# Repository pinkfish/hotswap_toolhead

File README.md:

# hotswap_toolhead (CAN stack, branch `can-stack`)

A CAN toolhead for 3D printers on two stacked boards. It drives a heater (up to 100 W) and a 24 V fan, and reads a thermistor (100k NTC or PT1000) and a switch. 24 V and the CAN bus come in on one small JST-XH plug. It runs Klipper over CAN on an STM32G0B1.

- **Boards:** two 25 × 26 mm, 4-layer boards, stacked 11 mm apart on a 2 × 4 board-to-board link: the logic board (MCU, CAN, USB, fan, sensors, 24 V input) on top and the power board (heater driver, 3.3 V buck) under it. Both have two M2 half-hole notches on their side edges for standoffs.
- **Plugs, all JST:**
  - Logic board, 6-pin XH on the top edge: 24 V and GND on two contacts each, CAN-H, CAN-L.
  - Logic board, 6-pin SH (1 mm) on the bottom edge: fan, thermistor, switch.
  - Logic board, 4-pin SH on the left edge: USB (VBUS, D−, D+, GND), wired to a USB socket for the first flash.
  - Power board, 4-pin XH on the bottom edge: the heater, two contacts per side.
- **Power:** an 8 A fuse and a TVS on the 24 V input, with no reverse-polarity FET (the plug is keyed). A 3.3 V buck runs the logic from 24 V or from USB alone.
- **Other branches:**
  - `can-sh` is the same circuit on one 27 × 34 mm board.
  - `usb-sh` is the USB-only board that one is built on: 19.5 × 23.5 mm, no heater.
  - `usb-only` is that board's first version.
  - `stack` is the 24 V CAN version as two stacked 27 × 27 mm boards, with XT30 and Nano-Fit plugs.
  - `narrow-27` and `centre-j2` are the earlier single-board 24 V versions.

## Repository layout

| Folder | Contents |
| --- | --- |
| `docs/` | Design spec (`design_spec.md`), with the Klipper config |
| `hardware/` | KiCad projects `toolhead_logic` and `toolhead_power`: schematics, routed PCBs, design rules, JLCPCB BOMs. `panel/`, `panel6/` and `panel4/` are the panels to order, each holding both boards |
| `gerber/` | Fab outputs. `logic/` and `power/` are the single boards, for checking. `panel/` (9 pairs), `panel6/` (6) and `panel4/` (4) are what you order: see `gerber/README.md` |
| `tools/` | See below |

What's in `tools/`:

- `design.py`: the netlist.
- `gen_kicad.py`: builds the schematic, BOM and rules from it.
- `verify.py`: checks every pin's net, and that the link's two halves match.
- `check_stack.py`: checks that the routed boards stack (outline, notches, link pins).
- `fab.sh`: regenerates `gerber/logic/` and `gerber/power/`.
- `make_panel.sh`: builds the panels.
- `layout/`: the placement and routing scripts (see `tools/layout/README.md`).

## Status

The schematic is complete and the PCB is routed:

- DRC: 0 errors, 0 unconnected, schematic parity clean, on both boards.
- `check_stack.py`: the boards stack.
- All three panels build with 0 DRC errors.

Nothing has been built or tested yet. See the prototype checks at the end of `docs/design_spec.md`, and note that the board has no reverse-polarity protection.

## Regenerating the KiCad files

```
python3 tools/gen_kicad.py   # rebuilds both schematics, BOMs and rules from tools/design.py
python3 tools/verify.py      # re-parses the schematic and checks every pin's net
```

The generator never touches the routed board. After a netlist change, choose one:

- Run **Update PCB from Schematic** in KiCad and fix up the routing.
- Re-run the layout (`tools/layout/run_stack.sh logic|power`).

Then run `tools/check_stack.py`, `tools/fab.sh` and `tools/make_panel.sh` (9, 6 and 4).

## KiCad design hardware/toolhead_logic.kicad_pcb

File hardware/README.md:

# CAN toolhead stack – KiCad projects

`tools/gen_kicad.py` generates both schematics from `tools/design.py`, the netlist. The PCBs are routed. The projects open in KiCad 8 or newer; they were routed and checked in KiCad 10.

## What's here

| File | Contents |
| --- | --- |
| `toolhead_logic.kicad_pro`, `.kicad_sch`, `.kicad_pcb`, `.kicad_dru` | The logic board (upper): 46 parts. Power input, MCU, CAN, USB, the plug J2, fan, thermistor, switch, the link socket J6. 25 × 26 mm, 4 layers, two M2 edge notches |
| `toolhead_power.kicad_pro`, `.kicad_sch`, `.kicad_pcb`, `.kicad_dru` | The power board (lower): 19 parts. The heater plug J3, heater FET and gate driver, 3.3 V buck, the link header J7. Same outline and notches |
| `toolhead_logic-bom-jlcpcb.csv`, `toolhead_power-bom-jlcpcb.csv`, `bom_jlcpcb.csv` | BOMs in JLCPCB's upload format, per board and for both together. The solder-jumper pads (JP1–JP3) are left out; every other part is placed |
| `panel/`, `panel6/`, `panel4/` | The panels to order: 9, 6 or 4 logic/power pairs, built by `../tools/make_panel.sh` |
| `fp-lib-table`, `footprints/` | Project footprint library: Q2's AOS DFN 3 × 3 footprint |

Netclasses (both boards): Power 0.8 / 0.3 mm, Fan 0.4 / 0.3 mm, Supply and USB 0.3 / 0.2 mm. The design rules add 0.8 mm minimum on the high-current nets, 0.3 mm clearance on the 24 V nets, the USB pair and the fan current.

`tools/verify.py` re-parses both schematics and rebuilds the netlists from pin and label positions: every pin matches `tools/design.py`, no pin is left dangling, and J6 and J7 carry the same net on every pin. `tools/check_stack.py` checks the routed boards: same outline and notches, and every J7 pin under its J6 contact.

## Layout

| Board | Layer | What's on it |
| --- | --- | --- |
| Logic | F.Cu | J1, J2, J5; F1, D1, F2; Q3, D5, R15, R16; LED1/LED2 with R5/R6. VIN_RAW and +24V pours. GND fill |
| Logic | B.Cu | U6 with Y1, FB1 and C9, C11–C15; CAN (U3, D4, R11, JP1, C16); J6; U5, C17, D3; C1; JP3 with R4, C10; the thermistor network and switch filter; SW1. +24V and GND pours on J6. GND fill |
| Power | F.Cu | J7, J3, Q2, U7 with R13, D10, C21, R14; C2; the buck (U1, L1, D9, D7, C4–C6, C8, R2, R3). +24V, HEAT_N and GND pours. GND fill |
| Power | B.Cu | GND fill; J7's pin ends |
| Both | In1 / In2 | Solid GND / signals |

- **Reference designators:** most bottom-side ones are on B.Fab rather than the silkscreen, because there is no room for them. They still appear on assembly drawings.

## Check against datasheets

- **J1 (JST S6B-XH-SM4-TB):** seen from the top with the plug opening at the top edge, pin 1 is on the right. 1–2 +24V, 3–4 GND, 5 CAN-H, 6 CAN-L.
- **J2 (JST SM06B-SRSS-TB):** plug opening at the bottom edge, pin 1 on the left. 1 FAN+, 2 FAN−, 3 TH_SIG, 4 thermistor GND, 5 SENS, 6 GND.
- **J5 (JST SM04B-SRSS-TB):** plug opening at the left edge, pin 1 at the top. 1 VBUS, 2 D−, 3 D+, 4 GND.
- **J3 (JST S4B-XH-SM4-TB, power board):** plug opening at the bottom edge, pin 1 on the left. 1–2 HEAT− (Q2's drain), 3–4 +24V.
- **J6/J7 (the link):** 1–2 +24V, 3, 4 and 6 GND, 5 VIN_LOGIC, 7 HEAT_PWM, 8 +3V3.
- **U1 (LMR16006XDDC):** 1 CB, 2 GND, 3 FB, 4 SHDN, 5 VIN, 6 SW.
- **U3 (TCAN3414DRBR):** 1 TXD, 2 GND, 3 VDD, 4 RXD, 5 SHDN (open), 6 CANL, 7 CANH, 8 STB (GND).
- **U7 (UCC27517DBVR):** 1 VDD, 2 GND, 3 IN+, 4 IN−, 5 OUT.
- **U6 STM32G0B1 pinout:** VREF+ 5, VDD/VDDA 6, VSS/VSSA 7, PB0/PB1 19/20, PB12/PB13 24/25, PA11/12 33/34, PA14/PA15 36/37, PD0 38, PB3 42. Confirm against ST DS13560.
- **Crystal Y1:** 20 pF load with 33 pF caps. Check the oscillator's gain margin (ST AN2867) on the first board.

## Net names

| Net | What it is |
| --- | --- |
| `VIN_RAW` | 24 V from J1, before F1 |
| `+24V` | After F1: the fan, the link to the heater and D7 |
| `HEAT_N` | Q2's drain, the heater's low side |
| `VIN_LOGIC` | The buck's input: +24V through D7 or VBUS through D3 |
| `GATE_12V` | U7's zener-clamped supply |
| `HEAT_PWM` | PD0 to U7, across the link |
| `VBUS` | USB 5 V from J5 |
| `+3V3` | The buck's output, across the link |
| `VREFP` | The ferrite-filtered ADC reference and thermistor pull-up |
| `CAN_H` / `CAN_L` | The bus |
| `FAN_P` / `FAN_N` | The fan + after F2, and Q3's drain |
| `TH_SIG` / `TH_ADC` | The thermistor, before and after its filter |
| `SENS` / `SENS_IN` | The switch, before and after its filter |

## Fab outputs

`../tools/fab.sh` exports `../gerber/logic/` and `../gerber/power/` with `kicad-cli`: 4-layer gerbers, drill files, the BOM and the CPL. `tools/jlc_cpl.py` writes each CPL by fitting each part's own JLCPCB footprint onto its pads. The panels are in `../gerber/panel*/`. `../gerber/README.md` says which files to upload.

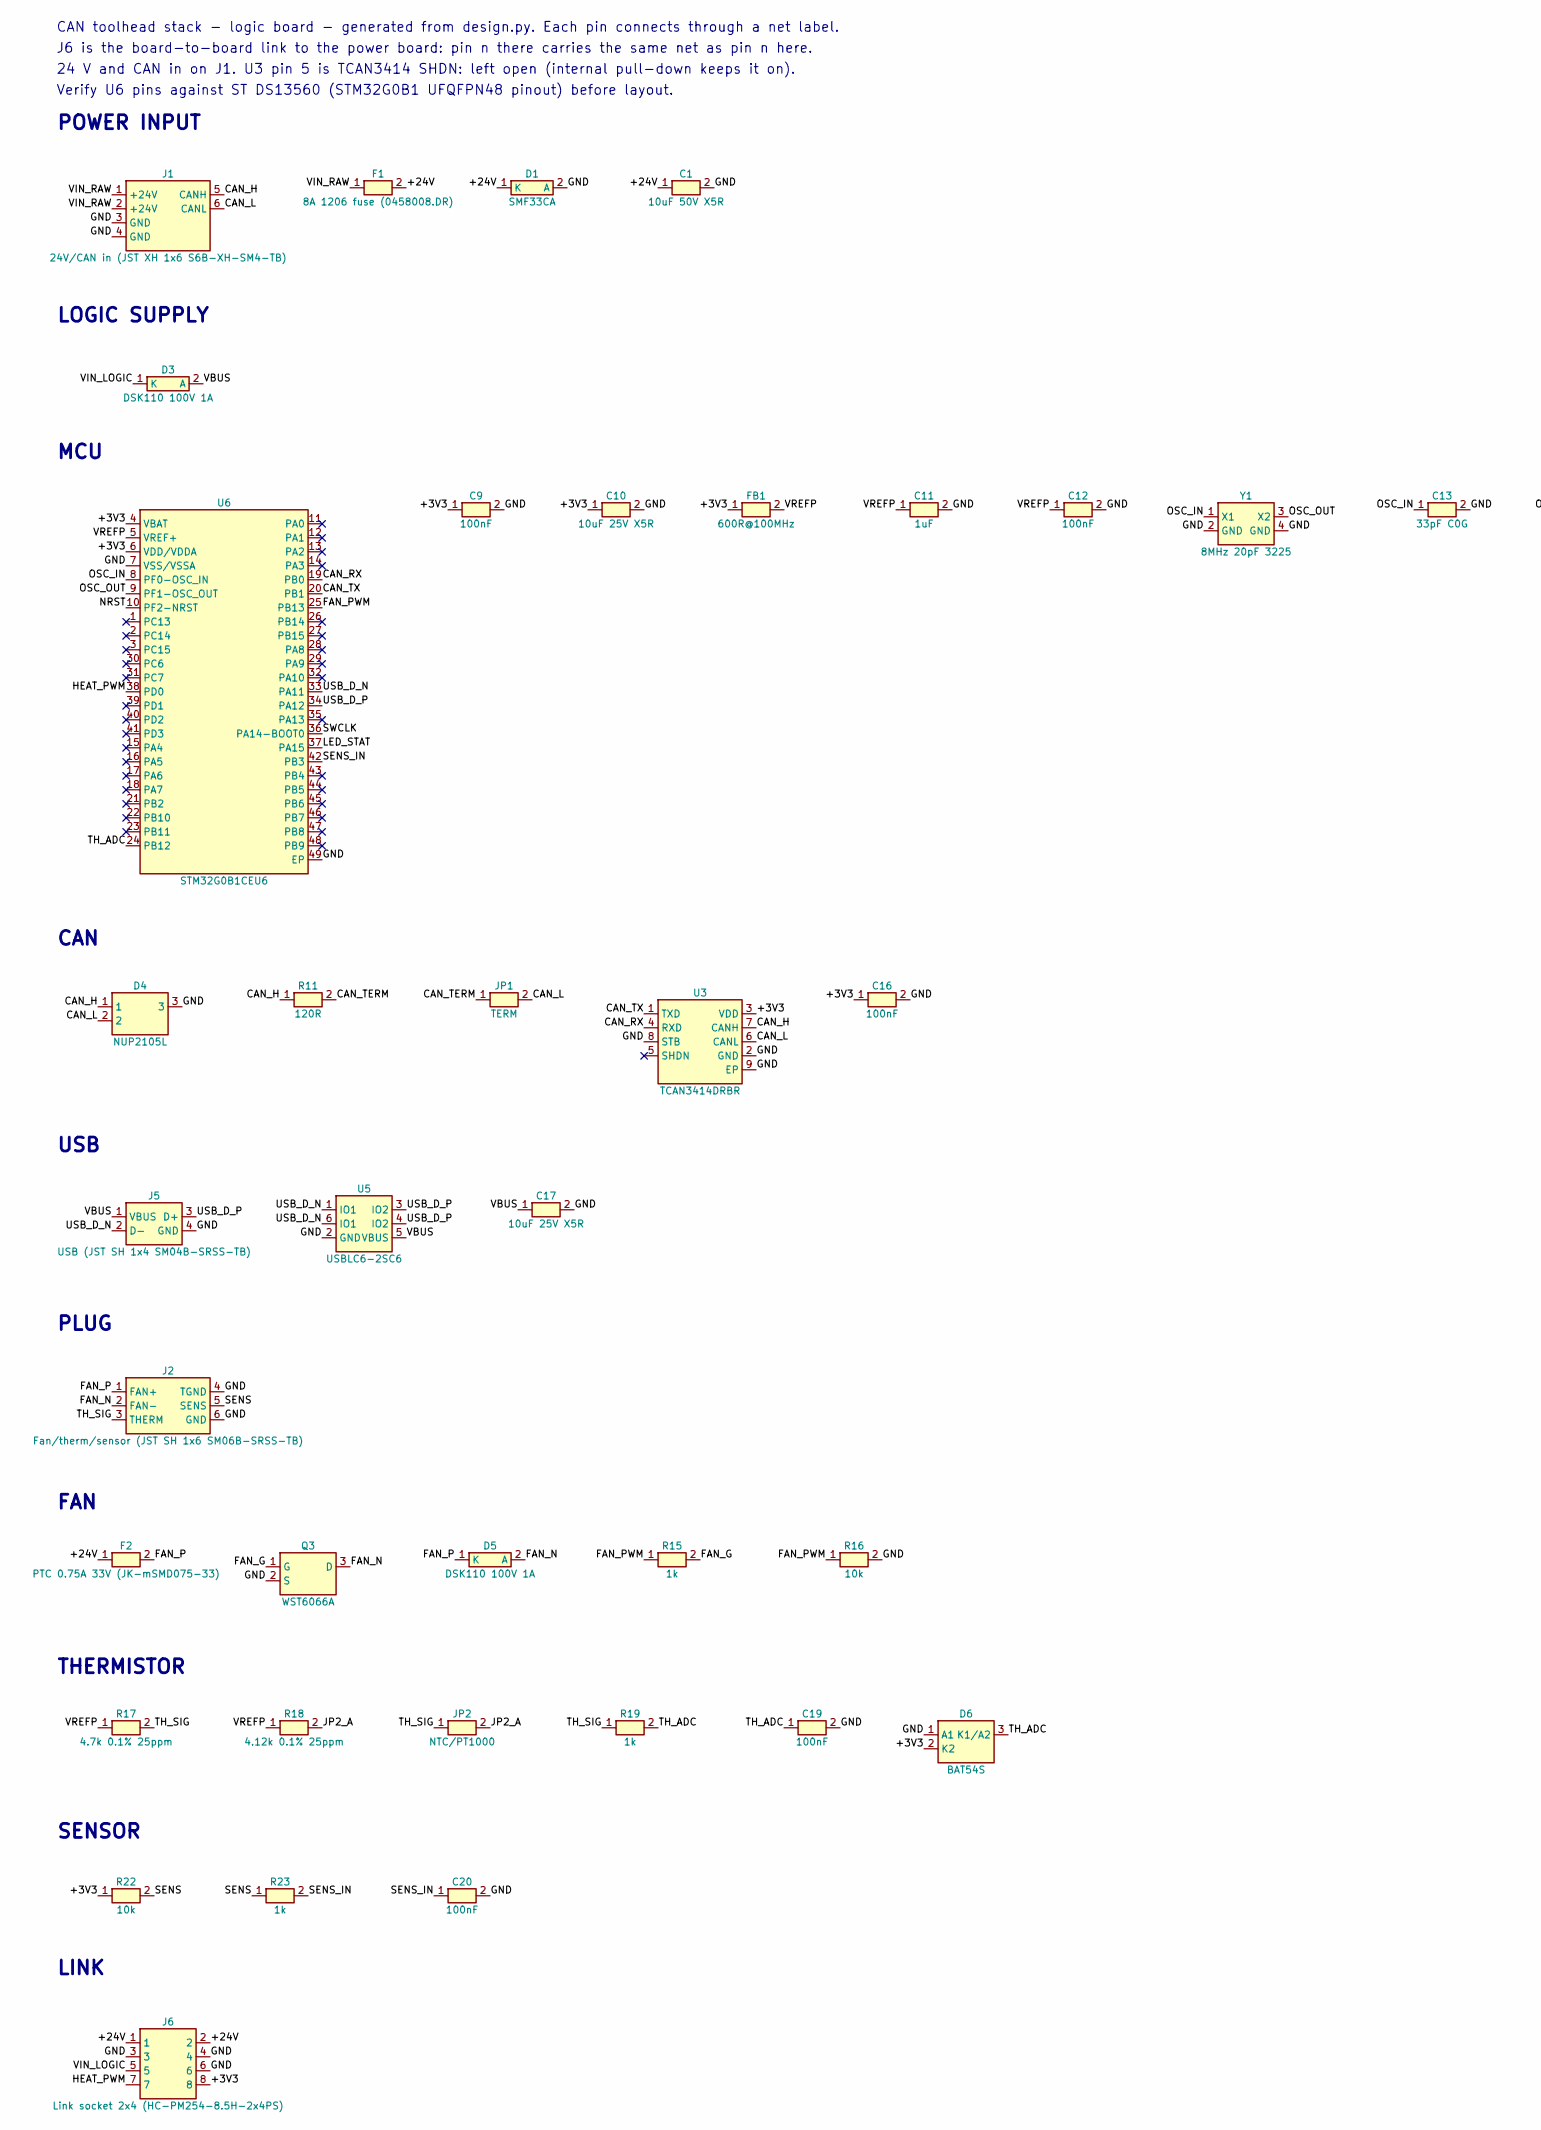
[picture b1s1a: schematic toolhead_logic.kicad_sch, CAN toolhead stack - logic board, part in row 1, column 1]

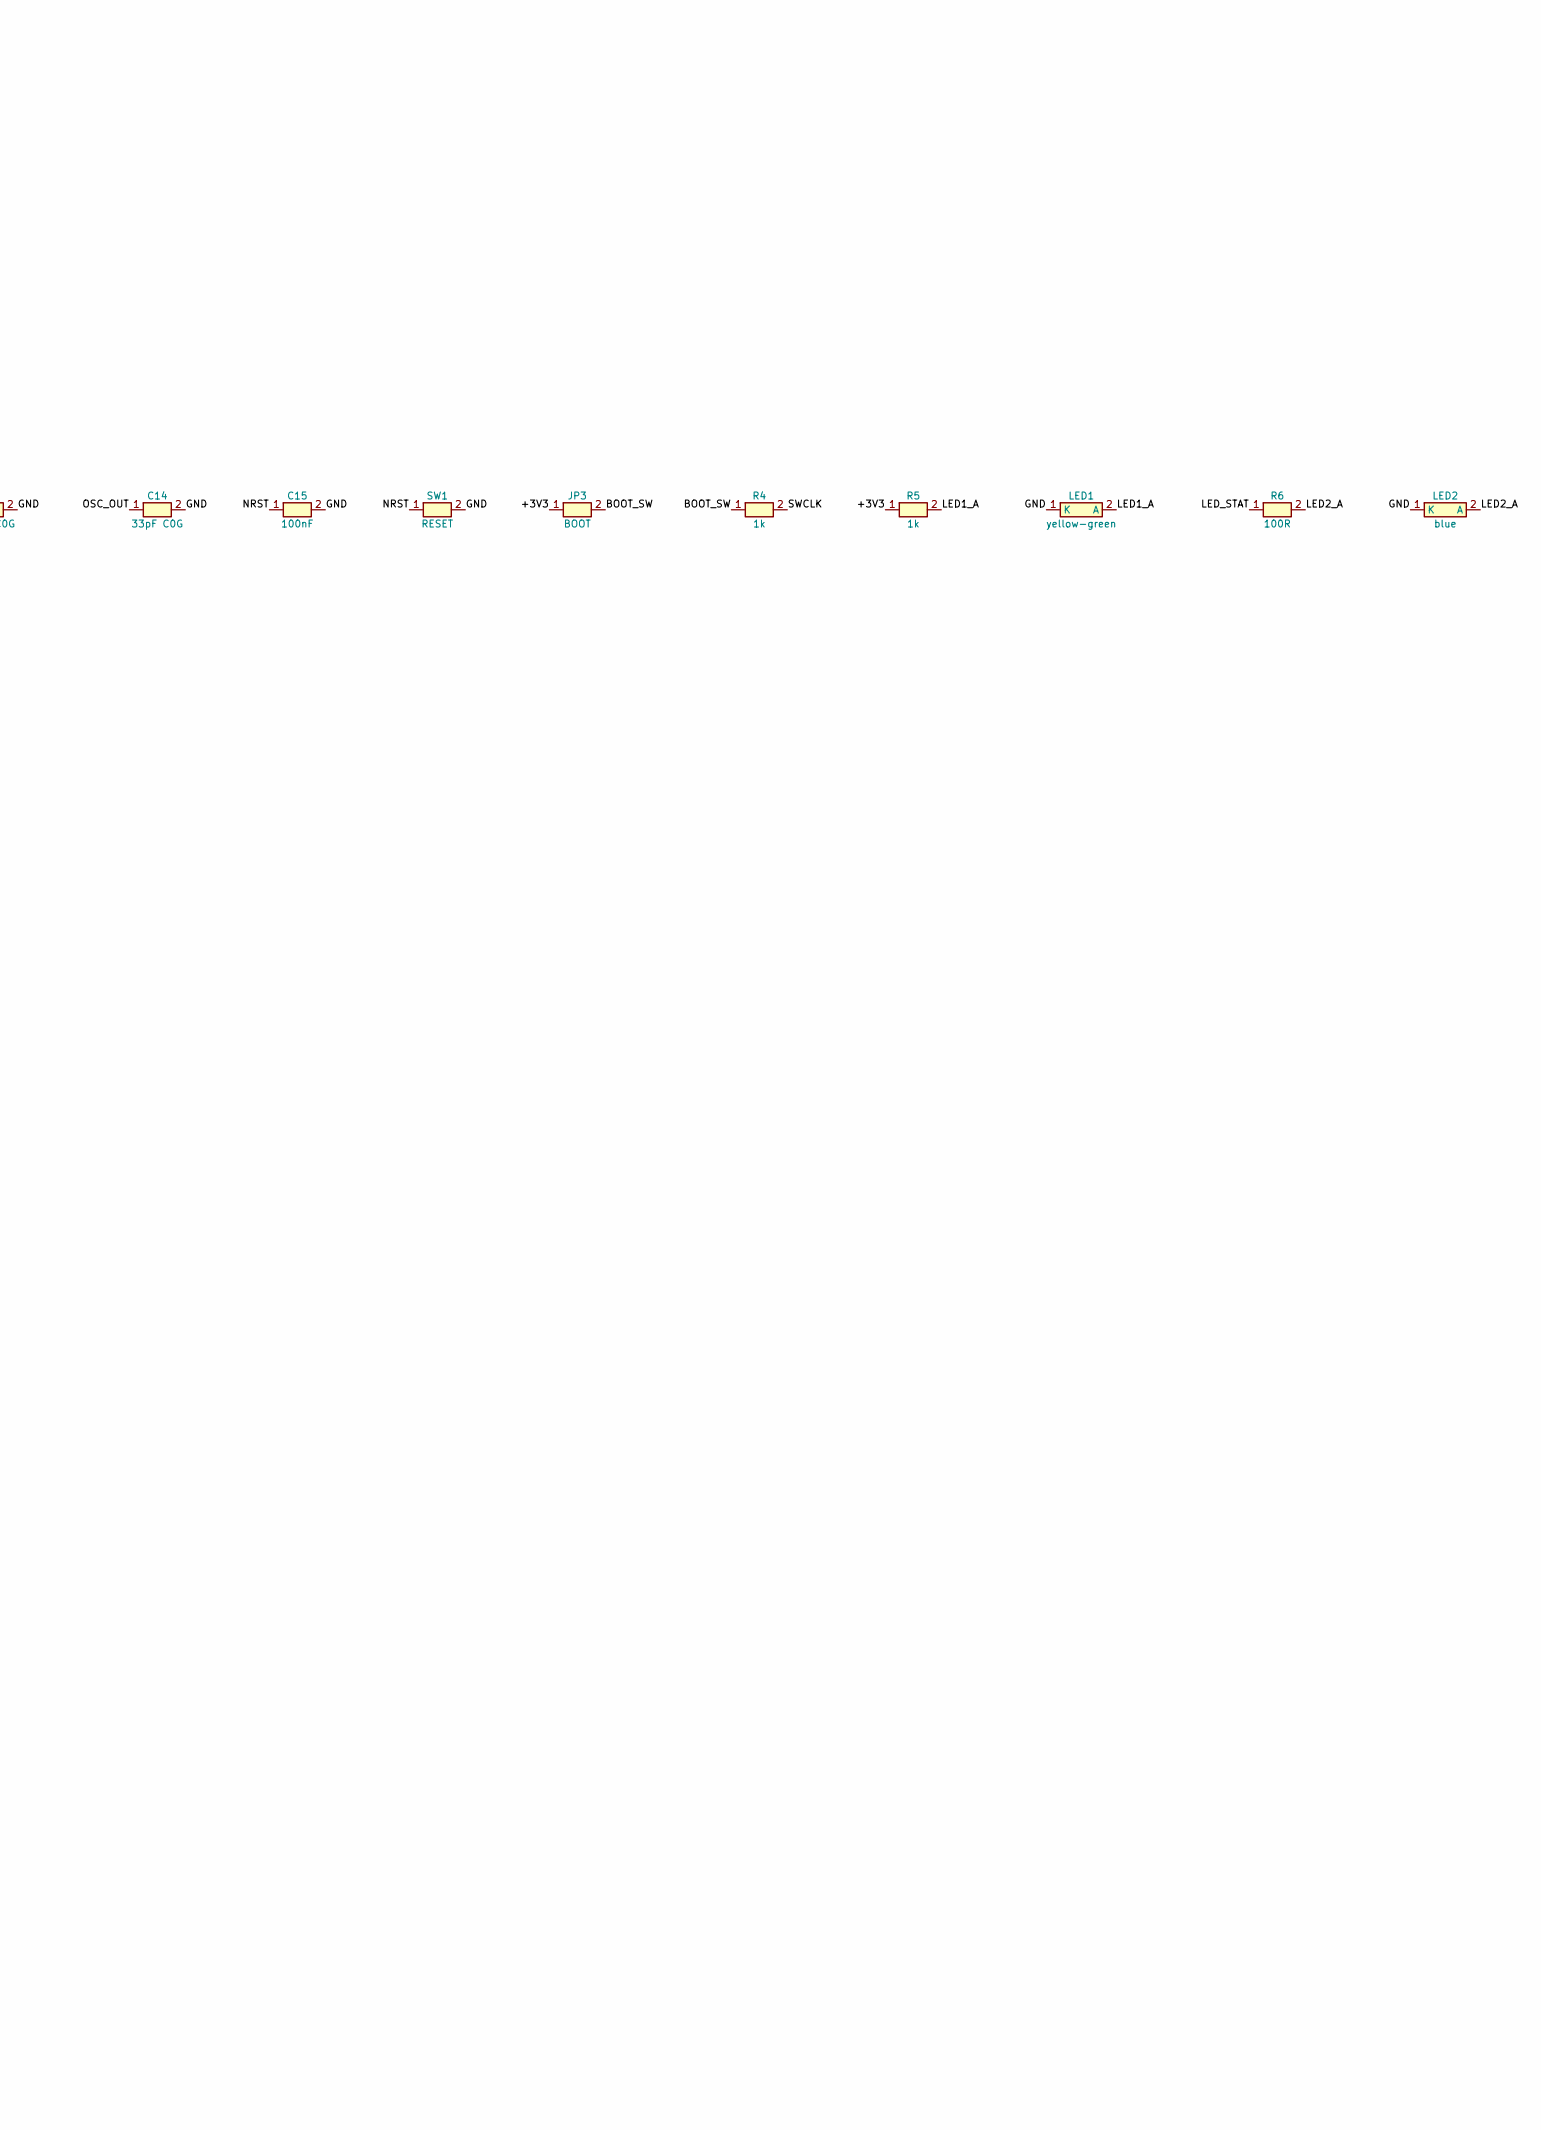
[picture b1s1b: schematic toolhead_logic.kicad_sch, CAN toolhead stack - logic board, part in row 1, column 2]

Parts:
C1: 10uF 50V X5R; C_1206_3216Metric; LCSC C13585
C9, C12, C15, C16, C19, C20: 100nF; C_0402_1005Metric; LCSC C1525
C10, C17: 10uF 25V X5R; C_0805_2012Metric; LCSC C15850
C11: 1uF; C_0402_1005Metric; LCSC C52923
C13, C14: 33pF C0G; C_0402_1005Metric; LCSC C1562
D1: SMF33CA; D_SOD-123F; LCSC C19077520
D3, D5: DSK110 100V 1A; D_SOD-123F; LCSC C22466354
D4: NUP2105L; SOT-23; LCSC C14486
D6: BAT54S; SOT-23; LCSC C7420333
F1: 8A 1206 fuse (0458008.DR); Fuse_1206_3216Metric; LCSC C187562
F2: PTC 0.75A 33V (JK-mSMD075-33); Fuse_1812_4532Metric; LCSC C369169
FB1: 600R@100MHz; L_0402_1005Metric; LCSC C76884
J1: 24V/CAN in (JST XH 1x6 S6B-XH-SM4-TB); JST_XH_S6B-XH-SM4-TB_1x06-1MP_P2.50mm_Horizontal; LCSC C191914
J2: Fan/therm/sensor (JST SH 1x6 SM06B-SRSS-TB); JST_SH_SM06B-SRSS-TB_1x06-1MP_P1.00mm_Horizontal; LCSC C160405
J5: USB (JST SH 1x4 SM04B-SRSS-TB); JST_SH_SM04B-SRSS-TB_1x04-1MP_P1.00mm_Horizontal; LCSC C160404
J6: Link socket 2x4 (HC-PM254-8.5H-2x4PS); PinSocket_2x04_P2.54mm_Vertical_SMD; LCSC C22373945
JP1: TERM; SolderJumper-2_P1.3mm_Open_RoundedPad1.0x1.5mm
JP2: NTC/PT1000; SolderJumper-2_P1.3mm_Open_RoundedPad1.0x1.5mm
JP3: BOOT; SolderJumper-2_P1.3mm_Open_RoundedPad1.0x1.5mm
LED1: yellow-green; LED_0603_1608Metric; LCSC C2289
LED2: blue; LED_0603_1608Metric; LCSC C2288
Q3: WST6066A; SOT-23; LCSC C148352
R4, R5, R15, R19, R23: 1k; R_0402_1005Metric; LCSC C11702
R6: 100R; R_0402_1005Metric; LCSC C25076
R11: 120R; R_0805_2012Metric; LCSC C17437
R16, R22: 10k; R_0402_1005Metric; LCSC C25744
R17: 4.7k 0.1% 25ppm; R_0402_1005Metric; LCSC C281778
R18: 4.12k 0.1% 25ppm; R_0402_1005Metric; LCSC C852812
SW1: RESET; SW_SPST_EVQP7C; LCSC C388883
U3: TCAN3414DRBR; VSON-8-1EP_3x3mm_P0.65mm_EP1.65x2.4mm; LCSC C31542495
U5: USBLC6-2SC6; SOT-23-6; LCSC C7519
U6: STM32G0B1CEU6; QFN-48-1EP_7x7mm_P0.5mm_EP5.6x5.6mm; LCSC C2829190
Y1: 8MHz 20pF 3225; Crystal_SMD_3225-4Pin_3.2x2.5mm; LCSC C2682774

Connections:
/+3V3: C9.1, C10.1, C16.1, D6.2 (K2), FB1.1, J6.8, JP3.1, R5.1, R22.1, U3.3 (VDD), U6.4 (VBAT), U6.6 (VDD/VDDA)
/+24V: C1.1, D1.1 (K), F1.2, F2.1, J6.1, J6.2
/BOOT_SW: JP3.2, R4.1
/CAN_H: D4.1, J1.5 (CANH), R11.1, U3.7 (CANH)
/CAN_L: D4.2, J1.6 (CANL), JP1.2, U3.6 (CANL)
/CAN_RX: U3.4 (RXD), U6.19 (PB0)
/CAN_TERM: JP1.1, R11.2
/CAN_TX: U3.1 (TXD), U6.20 (PB1)
/FAN_G: Q3.1 (G), R15.2
/FAN_N: D5.2 (A), J2.2 (FAN-), Q3.3 (D)
/FAN_P: D5.1 (K), F2.2, J2.1 (FAN+)
/FAN_PWM: R15.1, R16.1, U6.25 (PB13)
/GND: C1.2, C9.2, C10.2, C11.2, C12.2, C13.2, C14.2, C15.2, C16.2, C17.2, C19.2, C20.2, D1.2 (A), D4.3, D6.1 (A1), J1.3 (GND), J1.4 (GND), J2.4 (TGND), J2.6 (GND), J5.4 (GND), J6.3, J6.4, J6.6, LED1.1 (K), LED2.1 (K), Q3.2 (S), R16.2, SW1.2, U3.2 (GND), U3.8 (STB), U3.9 (EP), U5.2 (GND), U6.7 (VSS/VSSA), U6.49 (EP), Y1.2 (GND), Y1.4 (GND)
/HEAT_PWM: J6.7, U6.38 (PD0)
/JP2_A: JP2.2, R18.2
/LED1_A: LED1.2 (A), R5.2
/LED2_A: LED2.2 (A), R6.2
/LED_STAT: R6.1, U6.37 (PA15)
/NRST: C15.1, SW1.1, U6.10 (PF2-NRST)
/OSC_IN: C13.1, U6.8 (PF0-OSC_IN), Y1.1 (X1)
/OSC_OUT: C14.1, U6.9 (PF1-OSC_OUT), Y1.3 (X2)
/SENS: J2.5 (SENS), R22.2, R23.1
/SENS_IN: C20.1, R23.2, U6.42 (PB3)
/SWCLK: R4.2, U6.36 (PA14-BOOT0)
/TH_ADC: C19.1, D6.3 (K1/A2), R19.2, U6.24 (PB12)
/TH_SIG: J2.3 (THERM), JP2.1, R17.2, R19.1
/USB_D_N: J5.2 (D-), U5.1 (IO1), U5.6 (IO1), U6.33 (PA11)
/USB_D_P: J5.3 (D+), U5.3 (IO2), U5.4 (IO2), U6.34 (PA12)
/VBUS: C17.1, D3.2 (A), J5.1 (VBUS), U5.5 (VBUS)
/VIN_LOGIC: D3.1 (K), J6.5
/VIN_RAW: F1.1, J1.1 (+24V), J1.2 (+24V)
/VREFP: C11.1, C12.1, FB1.2, R17.1, R18.1, U6.5 (VREF+)

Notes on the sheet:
POWER INPUT
LOGIC SUPPLY
MCU
CAN
USB
PLUG
FAN
THERMISTOR
SENSOR
LINK
CAN toolhead stack - logic board - generated from design.py. Each pin connects through a net label.
J6 is the board-to-board link to the power board: pin n there carries the same net as pin n here.
24 V and CAN in on J1. U3 pin 5 is TCAN3414 SHDN: left open (internal pull-down keeps it on).
Verify U6 pins against ST DS13560 (STM32G0B1 UFQFPN48 pinout) before layout.

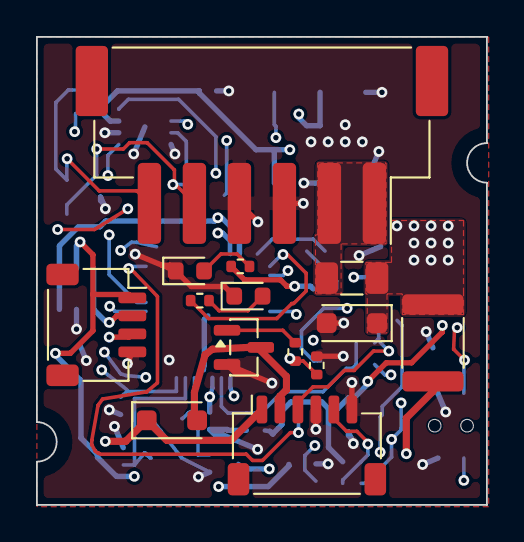
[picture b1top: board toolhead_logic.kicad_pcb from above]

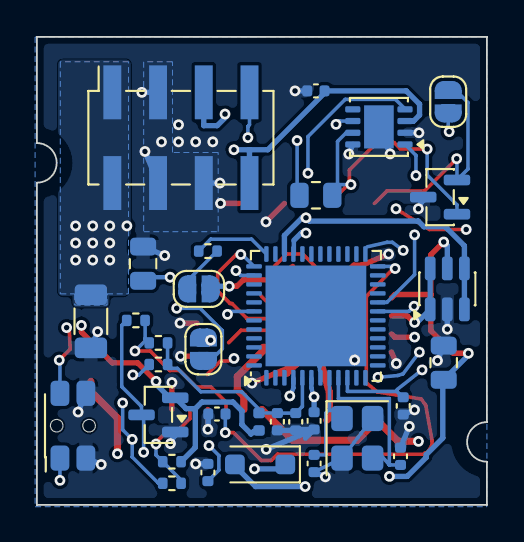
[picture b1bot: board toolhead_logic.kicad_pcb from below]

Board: 4 copper layers, 25.0 x 26.0 mm, 46 parts (32 on the bottom side), 32 nets.

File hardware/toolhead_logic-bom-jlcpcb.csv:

Comment,Designator,Footprint,LCSC Part #
100R,R6,R_0402_1005Metric,C25076
100nF,"C9,C12,C15,C16,C19,C20",C_0402_1005Metric,C1525
10k,"R16,R22",R_0402_1005Metric,C25744
10uF 25V X5R,"C10,C17",C_0805_2012Metric,C15850
10uF 50V X5R,C1,C_1206_3216Metric,C13585
120R,R11,R_0805_2012Metric,C17437
1k,"R4,R5,R15,R19,R23",R_0402_1005Metric,C11702
1uF,C11,C_0402_1005Metric,C52923
24V/CAN in (JST XH 1x6 S6B-XH-SM4-TB),J1,JST_XH_S6B-XH-SM4-TB_1x06-1MP_P2.50mm_Horizontal,C191914
33pF C0G,"C13,C14",C_0402_1005Metric,C1562
4.12k 0.1% 25ppm,R18,R_0402_1005Metric,C852812
4.7k 0.1% 25ppm,R17,R_0402_1005Metric,C281778
600R@100MHz,FB1,L_0402_1005Metric,C76884
8A 1206 fuse (0458008.DR),F1,Fuse_1206_3216Metric,C187562
8MHz 20pF 3225,Y1,Crystal_SMD_3225-4Pin_3.2x2.5mm,C2682774
BAT54S,D6,SOT-23,C7420333
DSK110 100V 1A,"D3,D5",D_SOD-123F,C22466354
Fan/therm/sensor (JST SH 1x6 SM06B-SRSS-TB),J2,JST_SH_SM06B-SRSS-TB_1x06-1MP_P1.00mm_Horizontal,C160405
Link socket 2x4 (HC-PM254-8.5H-2x4PS),J6,PinSocket_2x04_P2.54mm_Vertical_SMD,C22373945
NUP2105L,D4,SOT-23,C14486
PTC 0.75A 33V (JK-mSMD075-33),F2,Fuse_1812_4532Metric,C369169
RESET,SW1,SW_SPST_EVQP7C,C388883
SMF33CA,D1,D_SOD-123F,C19077520
STM32G0B1CEU6,U6,QFN-48-1EP_7x7mm_P0.5mm_EP5.6x5.6mm,C2829190
TCAN3414DRBR,U3,VSON-8-1EP_3x3mm_P0.65mm_EP1.65x2.4mm,C31542495
USB (JST SH 1x4 SM04B-SRSS-TB),J5,JST_SH_SM04B-SRSS-TB_1x04-1MP_P1.00mm_Horizontal,C160404
USBLC6-2SC6,U5,SOT-23-6,C7519
WST6066A,Q3,SOT-23,C148352
blue,LED2,LED_0603_1608Metric,C2288
yellow-green,LED1,LED_0603_1608Metric,C2289

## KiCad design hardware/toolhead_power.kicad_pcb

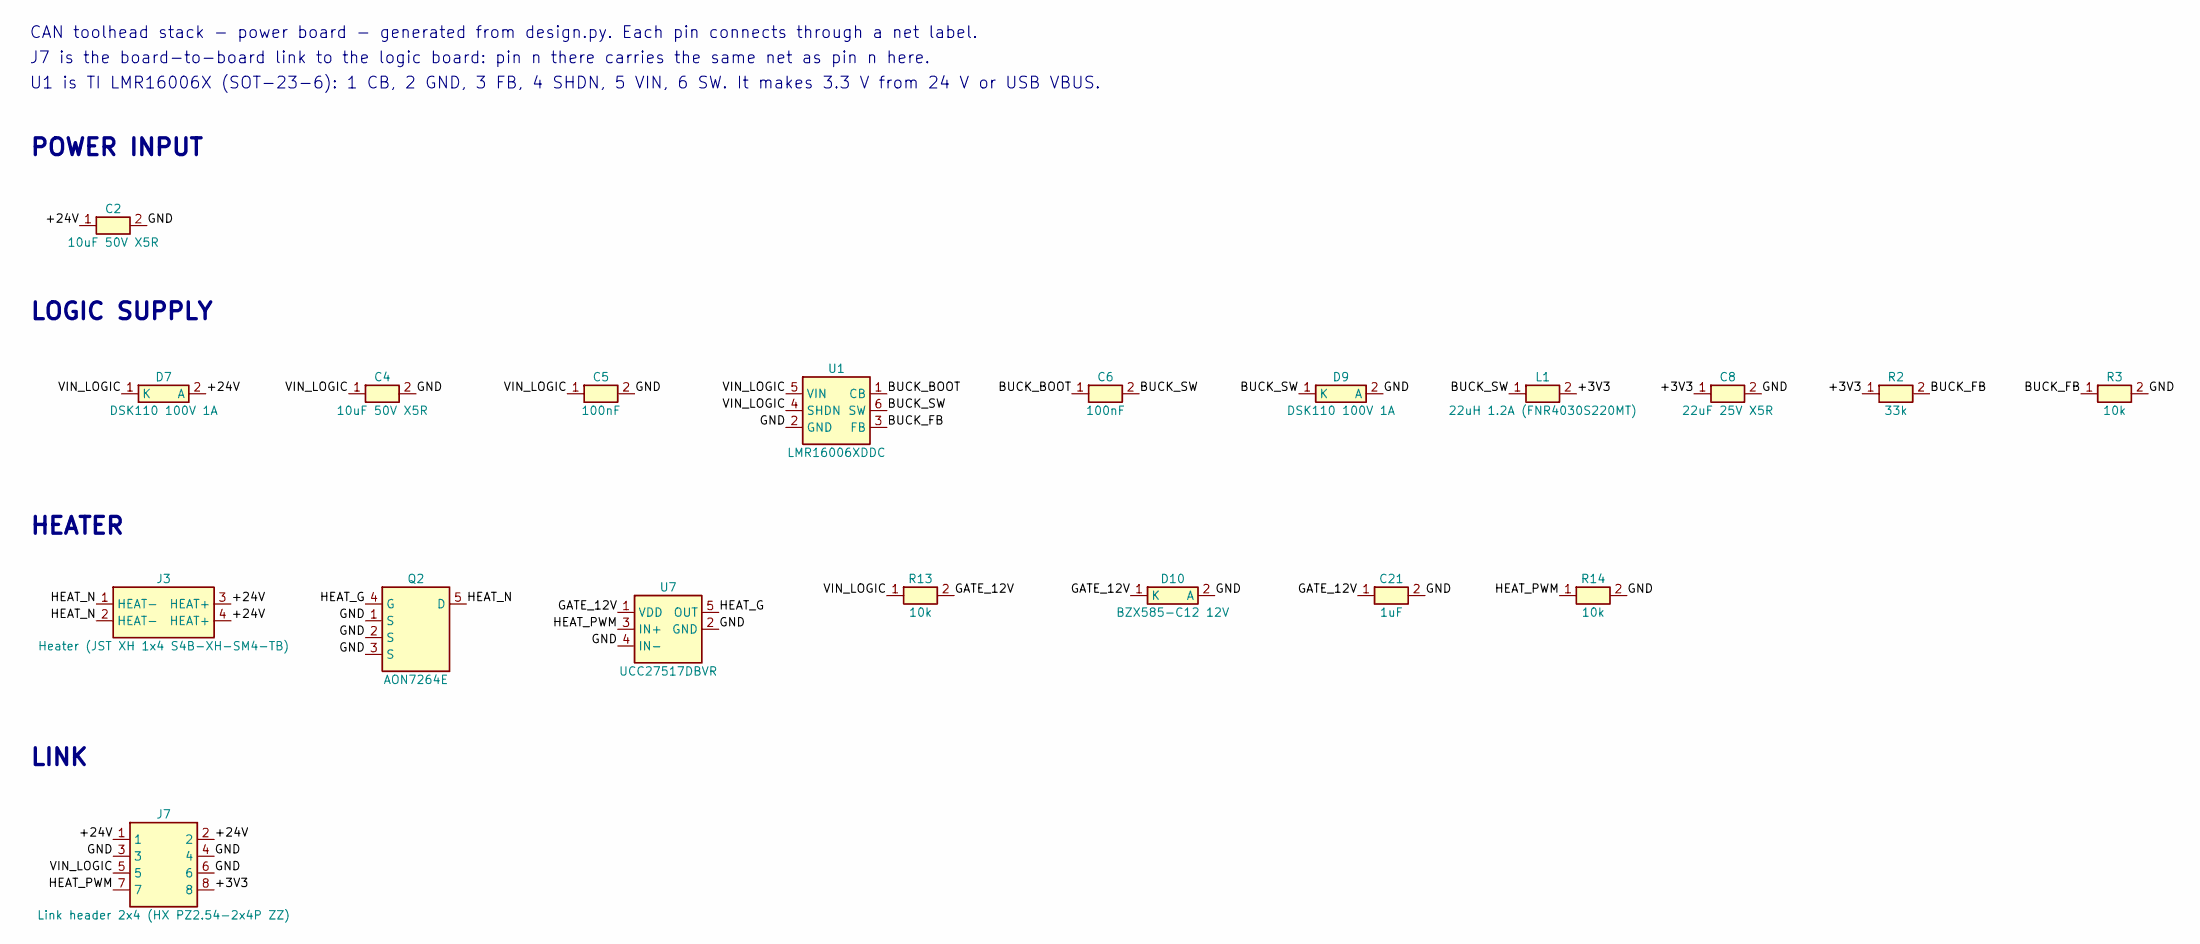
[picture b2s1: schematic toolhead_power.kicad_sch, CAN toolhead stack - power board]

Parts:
C2, C4: 10uF 50V X5R; C_1206_3216Metric; LCSC C13585
C5: 100nF; C_0603_1608Metric; LCSC C14663
C6: 100nF; C_0402_1005Metric; LCSC C1525
C8: 22uF 25V X5R; C_1206_3216Metric; LCSC C12891
C21: 1uF; C_0402_1005Metric; LCSC C52923
D7, D9: DSK110 100V 1A; D_SOD-123F; LCSC C22466354
D10: BZX585-C12 12V; D_SOD-523; LCSC C455018
J3: Heater (JST XH 1x4 S4B-XH-SM4-TB); JST_XH_S4B-XH-SM4-TB_1x04-1MP_P2.50mm_Horizontal; LCSC C161861
J7: Link header 2x4 (HX PZ2.54-2x4P ZZ); PinHeader_2x04_P2.54mm_Vertical; LCSC C32713277
L1: 22uH 1.2A (FNR4030S220MT); L_Taiyo-Yuden_NR-40xx; LCSC C167883
Q2: AON7264E; AOS_DFN-8-1EP_3x3mm_P0.65mm; LCSC C431191
R2: 33k; R_0402_1005Metric; LCSC C25779
R3, R13, R14: 10k; R_0402_1005Metric; LCSC C25744
U1: LMR16006XDDC; SOT-23-6; LCSC C87080
U7: UCC27517DBVR; SOT-23-5; LCSC C99395

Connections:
/+3V3: C8.1, J7.8, L1.2, R2.1
/+24V: C2.1, D7.2 (A), J3.3 (HEAT+), J3.4 (HEAT+), J7.1, J7.2
/BUCK_BOOT: C6.1, U1.1 (CB)
/BUCK_FB: R2.2, R3.1, U1.3 (FB)
/BUCK_SW: C6.2, D9.1 (K), L1.1, U1.6 (SW)
/GATE_12V: C21.1, D10.1 (K), R13.2, U7.1 (VDD)
/GND: C2.2, C4.2, C5.2, C8.2, C21.2, D9.2 (A), D10.2 (A), J7.3, J7.4, J7.6, Q2.1 (S), Q2.2 (S), Q2.3 (S), R3.2, R14.2, U1.2 (GND), U7.2 (GND), U7.4 (IN-)
/HEAT_G: Q2.4 (G), U7.5 (OUT)
/HEAT_N: J3.1 (HEAT-), J3.2 (HEAT-), Q2.5 (D)
/HEAT_PWM: J7.7, R14.1, U7.3 (IN+)
/VIN_LOGIC: C4.1, C5.1, D7.1 (K), J7.5, R13.1, U1.4 (SHDN), U1.5 (VIN)

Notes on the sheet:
POWER INPUT
LOGIC SUPPLY
HEATER
LINK
CAN toolhead stack - power board - generated from design.py. Each pin connects through a net label.
J7 is the board-to-board link to the logic board: pin n there carries the same net as pin n here.
U1 is TI LMR16006X (SOT-23-6): 1 CB, 2 GND, 3 FB, 4 SHDN, 5 VIN, 6 SW. It makes 3.3 V from 24 V or USB VBUS.

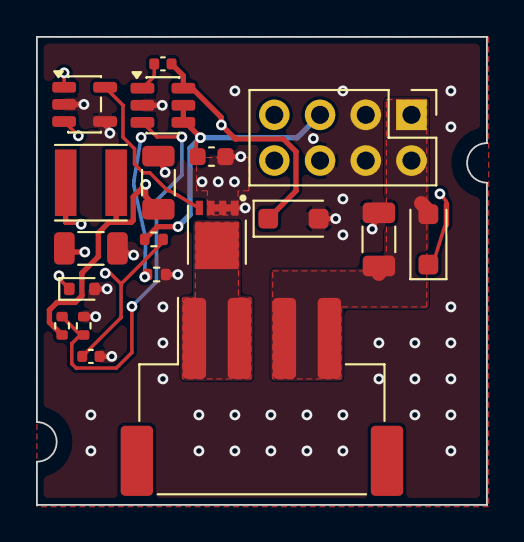
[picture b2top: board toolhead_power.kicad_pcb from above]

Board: 4 copper layers, 25.0 x 26.0 mm, 19 parts (0 on the bottom side), 11 nets.
